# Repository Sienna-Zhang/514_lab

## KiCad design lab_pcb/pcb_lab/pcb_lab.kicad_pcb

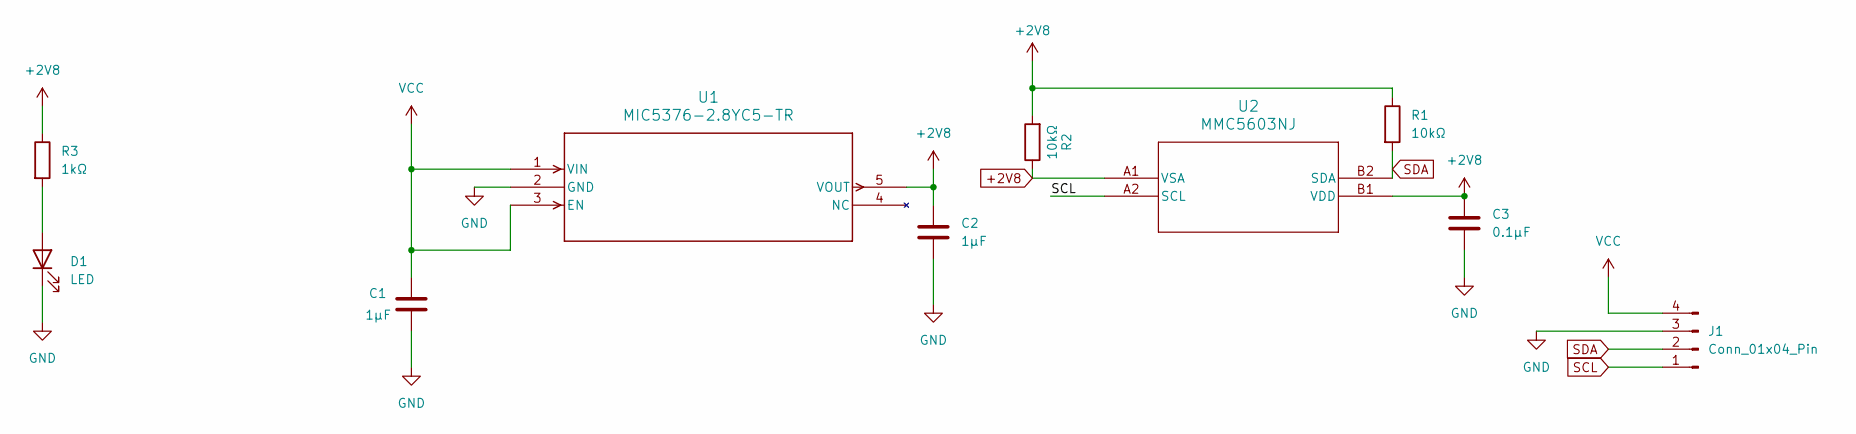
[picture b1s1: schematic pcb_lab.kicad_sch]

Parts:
C1, C2: 1μF; C_0805_2012Metric_Pad1.18x1.45mm_HandSolder
C3: 0.1μF; C_0805_2012Metric_Pad1.18x1.45mm_HandSolder
D1: LED; LED_0805_2012Metric_Pad1.15x1.40mm_HandSolder
J1: Conn_01x04_Pin; PinHeader_1x04_P2.54mm_Vertical
R1, R2: 10kΩ; R_0805_2012Metric_Pad1.20x1.40mm_HandSolder
R3: 1kΩ; R_0805_2012Metric_Pad1.20x1.40mm_HandSolder
U1: MIC5376-2.8YC5-TR; SC-70_C5_MCH-L
U2: MMC5603NJ; WLP4_0P82X0P82_MEM-L

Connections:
+2V8: C2.1, C3.1, R1.1, R2.1, R2.2, R3.1, U1.5 (VOUT), U2.A1 (VSA), U2.B1 (VDD)
GND: C1.2, C2.2, C3.2, D1.1 (K), J1.3, U1.2 (GND)
unnamed: D1.2 (A), R3.2
SCL: J1.1, U2.A2 (SCL)
SDA: J1.2, R1.2, U2.B2 (SDA)
VCC: C1.1, J1.4, U1.1 (VIN), U1.3 (EN)

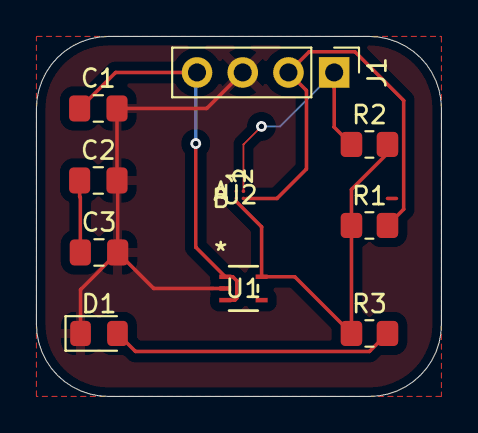
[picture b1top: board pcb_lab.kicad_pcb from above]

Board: 2 copper layers, 22.5 x 20.0 mm, 10 parts (0 on the bottom side), 6 nets.

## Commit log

2026-01-26 wireless
2026-01-30 pcb lab
2026-02-05 lab5
